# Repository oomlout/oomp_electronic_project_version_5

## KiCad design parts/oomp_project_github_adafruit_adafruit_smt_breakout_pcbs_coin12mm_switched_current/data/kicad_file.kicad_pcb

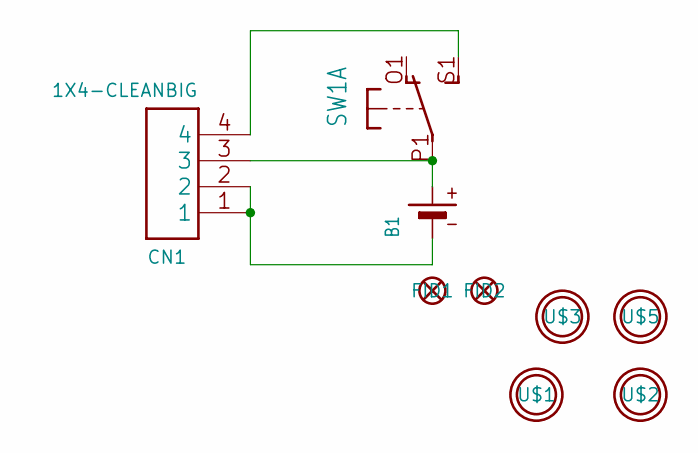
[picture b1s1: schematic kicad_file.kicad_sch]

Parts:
B1: BATTERYCR1220_SMT; CR1220
CN1: 1X4-CLEANBIG; 1X04-CLEANBIG
FID1, FID2: FIDUCIAL""; FIDUCIAL_1MM
SW1: DPDT-EG1390; EG1390
U$1, U$2, U$3, U$5: MOUNTINGHOLE2.5; MOUNTINGHOLE_2.5_PLATED

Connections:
3V: B1.+$1 (+), CN1.3, SW1.P1
unnamed: B1.-, CN1.1, CN1.2
unnamed: CN1.4, SW1.S1 (S)

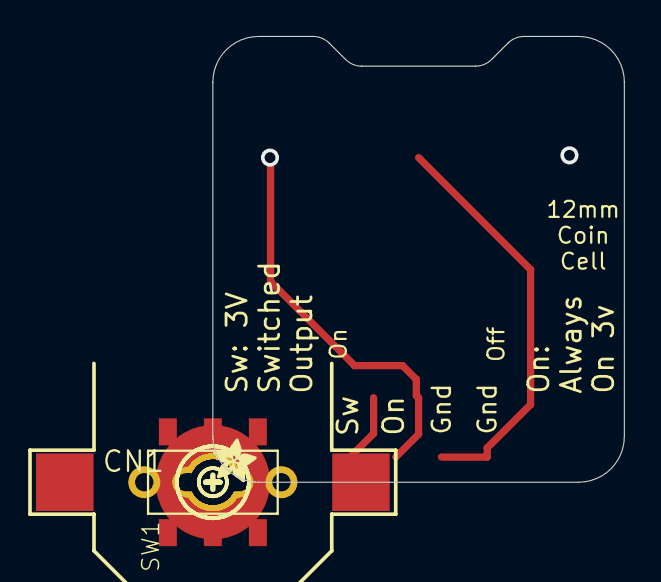
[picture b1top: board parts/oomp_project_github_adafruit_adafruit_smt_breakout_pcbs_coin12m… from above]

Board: 2 copper layers, 22.9 x 24.8 mm, 12 parts (0 on the bottom side), 3 nets.

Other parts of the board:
U$6: SYMBOL_PLUS
U$7: SYMBOL_MINUS
U$8: ADAFRUIT_2.5MM

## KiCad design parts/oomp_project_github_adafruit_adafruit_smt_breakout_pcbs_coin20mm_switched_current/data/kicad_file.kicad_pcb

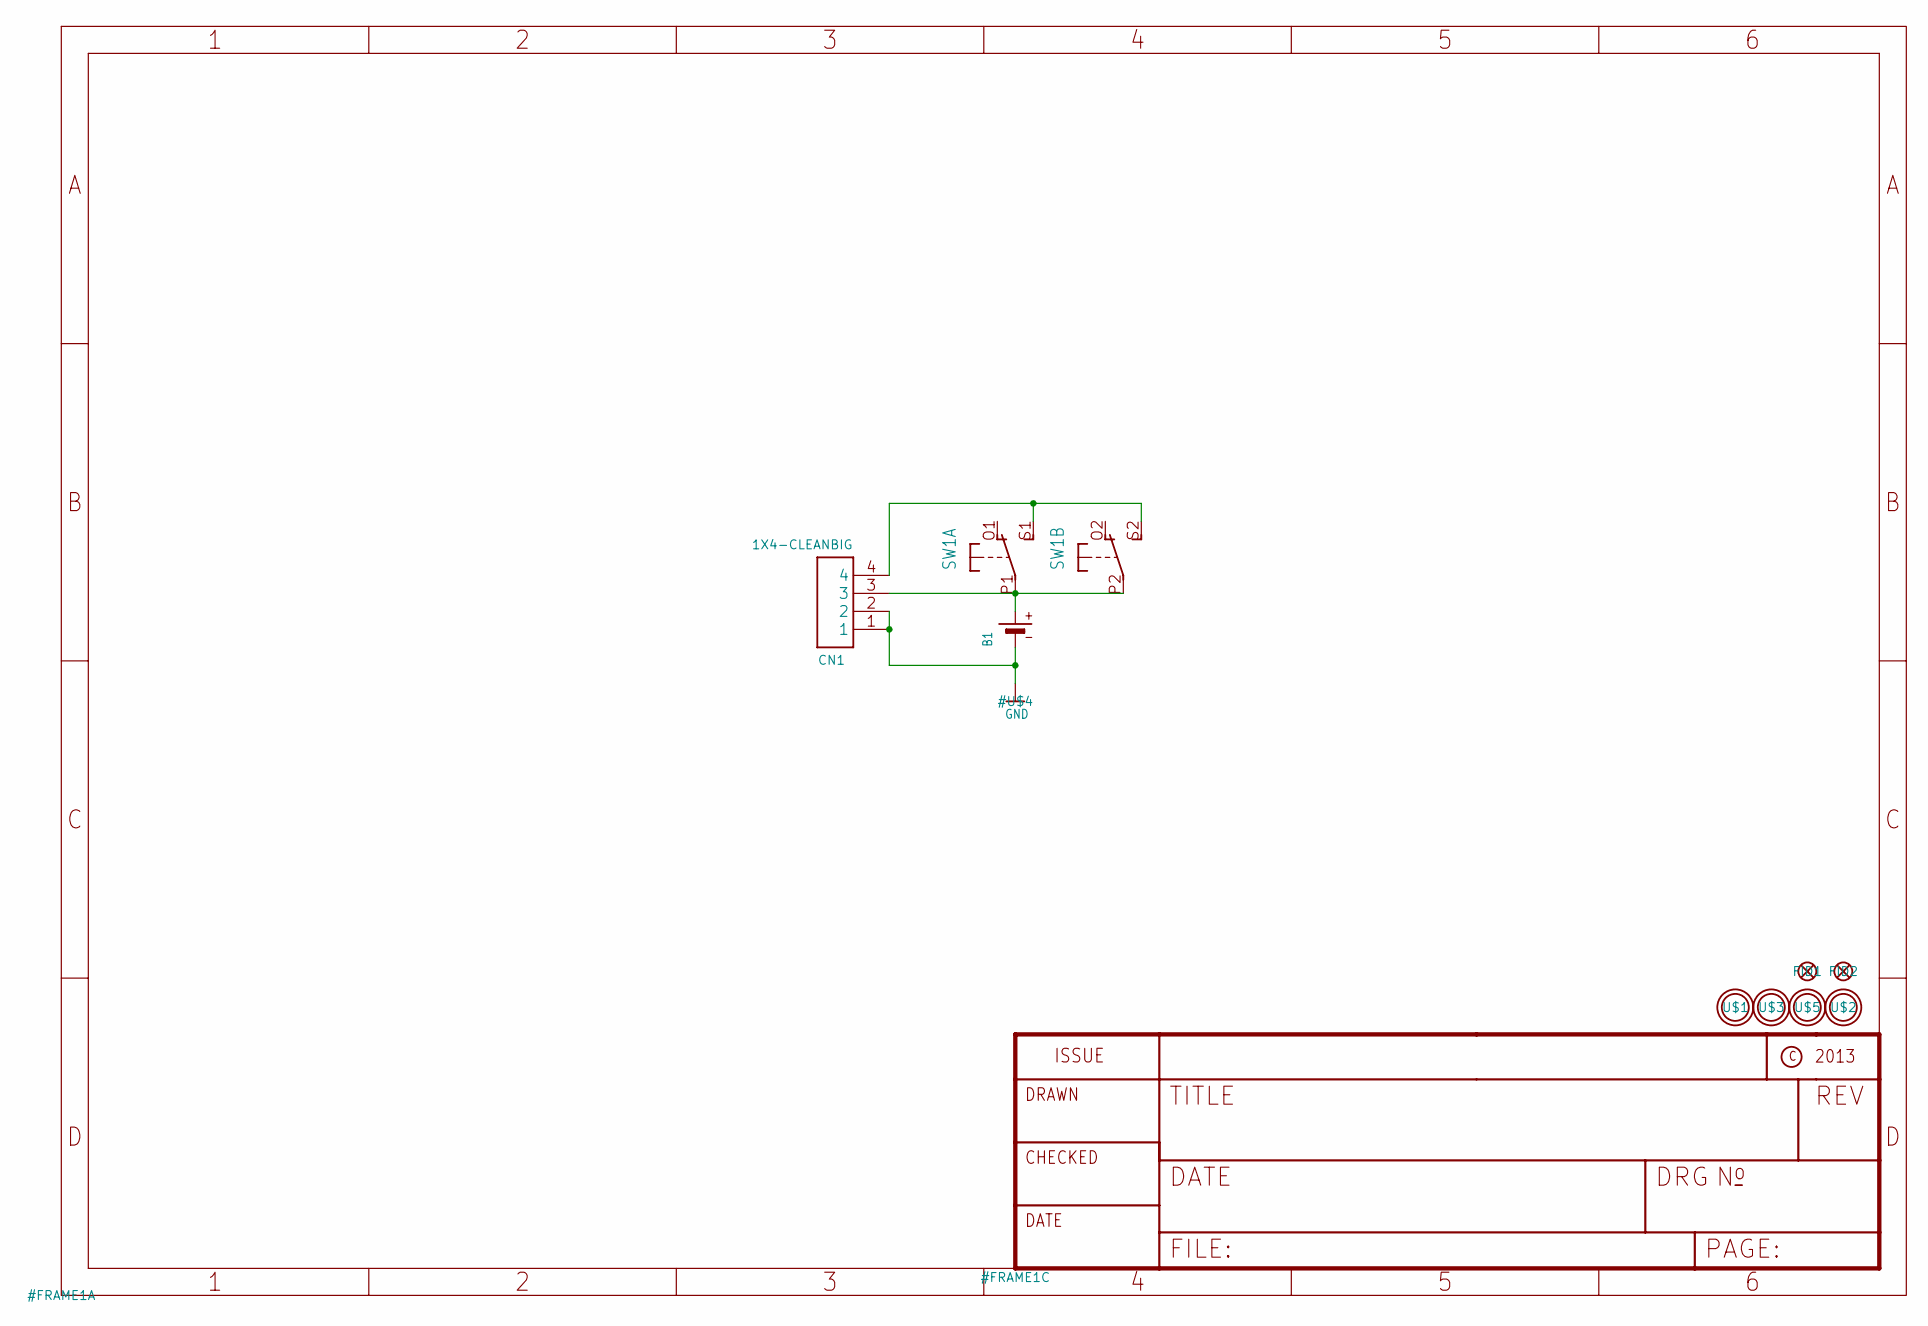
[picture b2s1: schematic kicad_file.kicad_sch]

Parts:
B1: BATTERYCR2032_BAT-HLD-001; CR2032_SMT_BAT-HLD-001
CN1: 1X4-CLEANBIG; 1X04-CLEANBIG
FID1, FID2: FIDUCIAL""; FIDUCIAL_1MM
SW1: DPDT-EG1390; EG1390
U$1, U$2, U$3, U$5: MOUNTINGHOLE2.5; MOUNTINGHOLE_2.5_PLATED

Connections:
3V: B1.+$1 (+), B1.+$2 (+), CN1.3, SW1.P1, SW1.P2
GND: B1.-, CN1.1, CN1.2
unnamed: CN1.4, SW1.S1 (S), SW1.S2 (S)

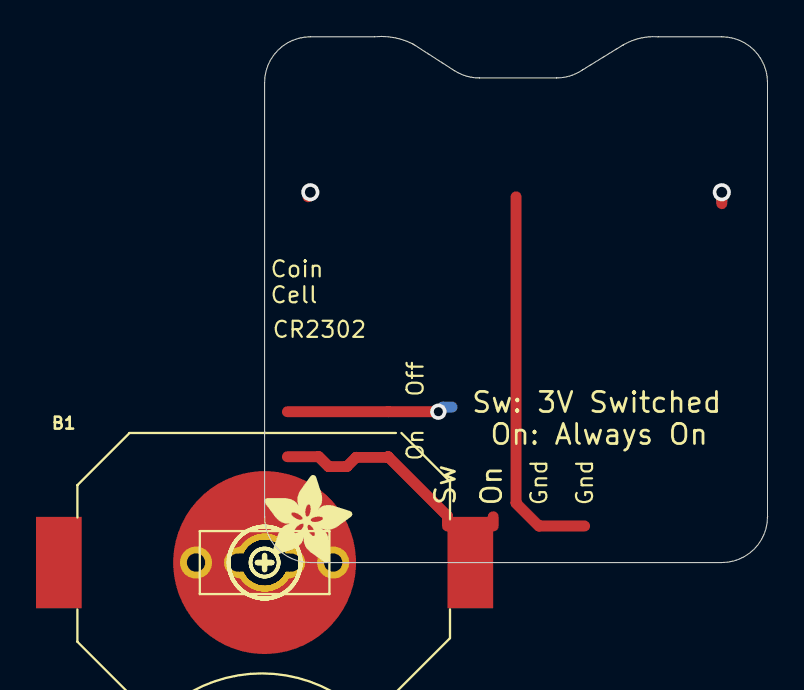
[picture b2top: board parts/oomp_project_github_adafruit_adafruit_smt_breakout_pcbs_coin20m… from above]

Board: 2 copper layers, 27.9 x 29.2 mm, 12 parts (0 on the bottom side), 3 nets.

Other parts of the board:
U$6: SYMBOL_PLUS
U$7: SYMBOL_MINUS
U$8: ADAFRUIT_5MM

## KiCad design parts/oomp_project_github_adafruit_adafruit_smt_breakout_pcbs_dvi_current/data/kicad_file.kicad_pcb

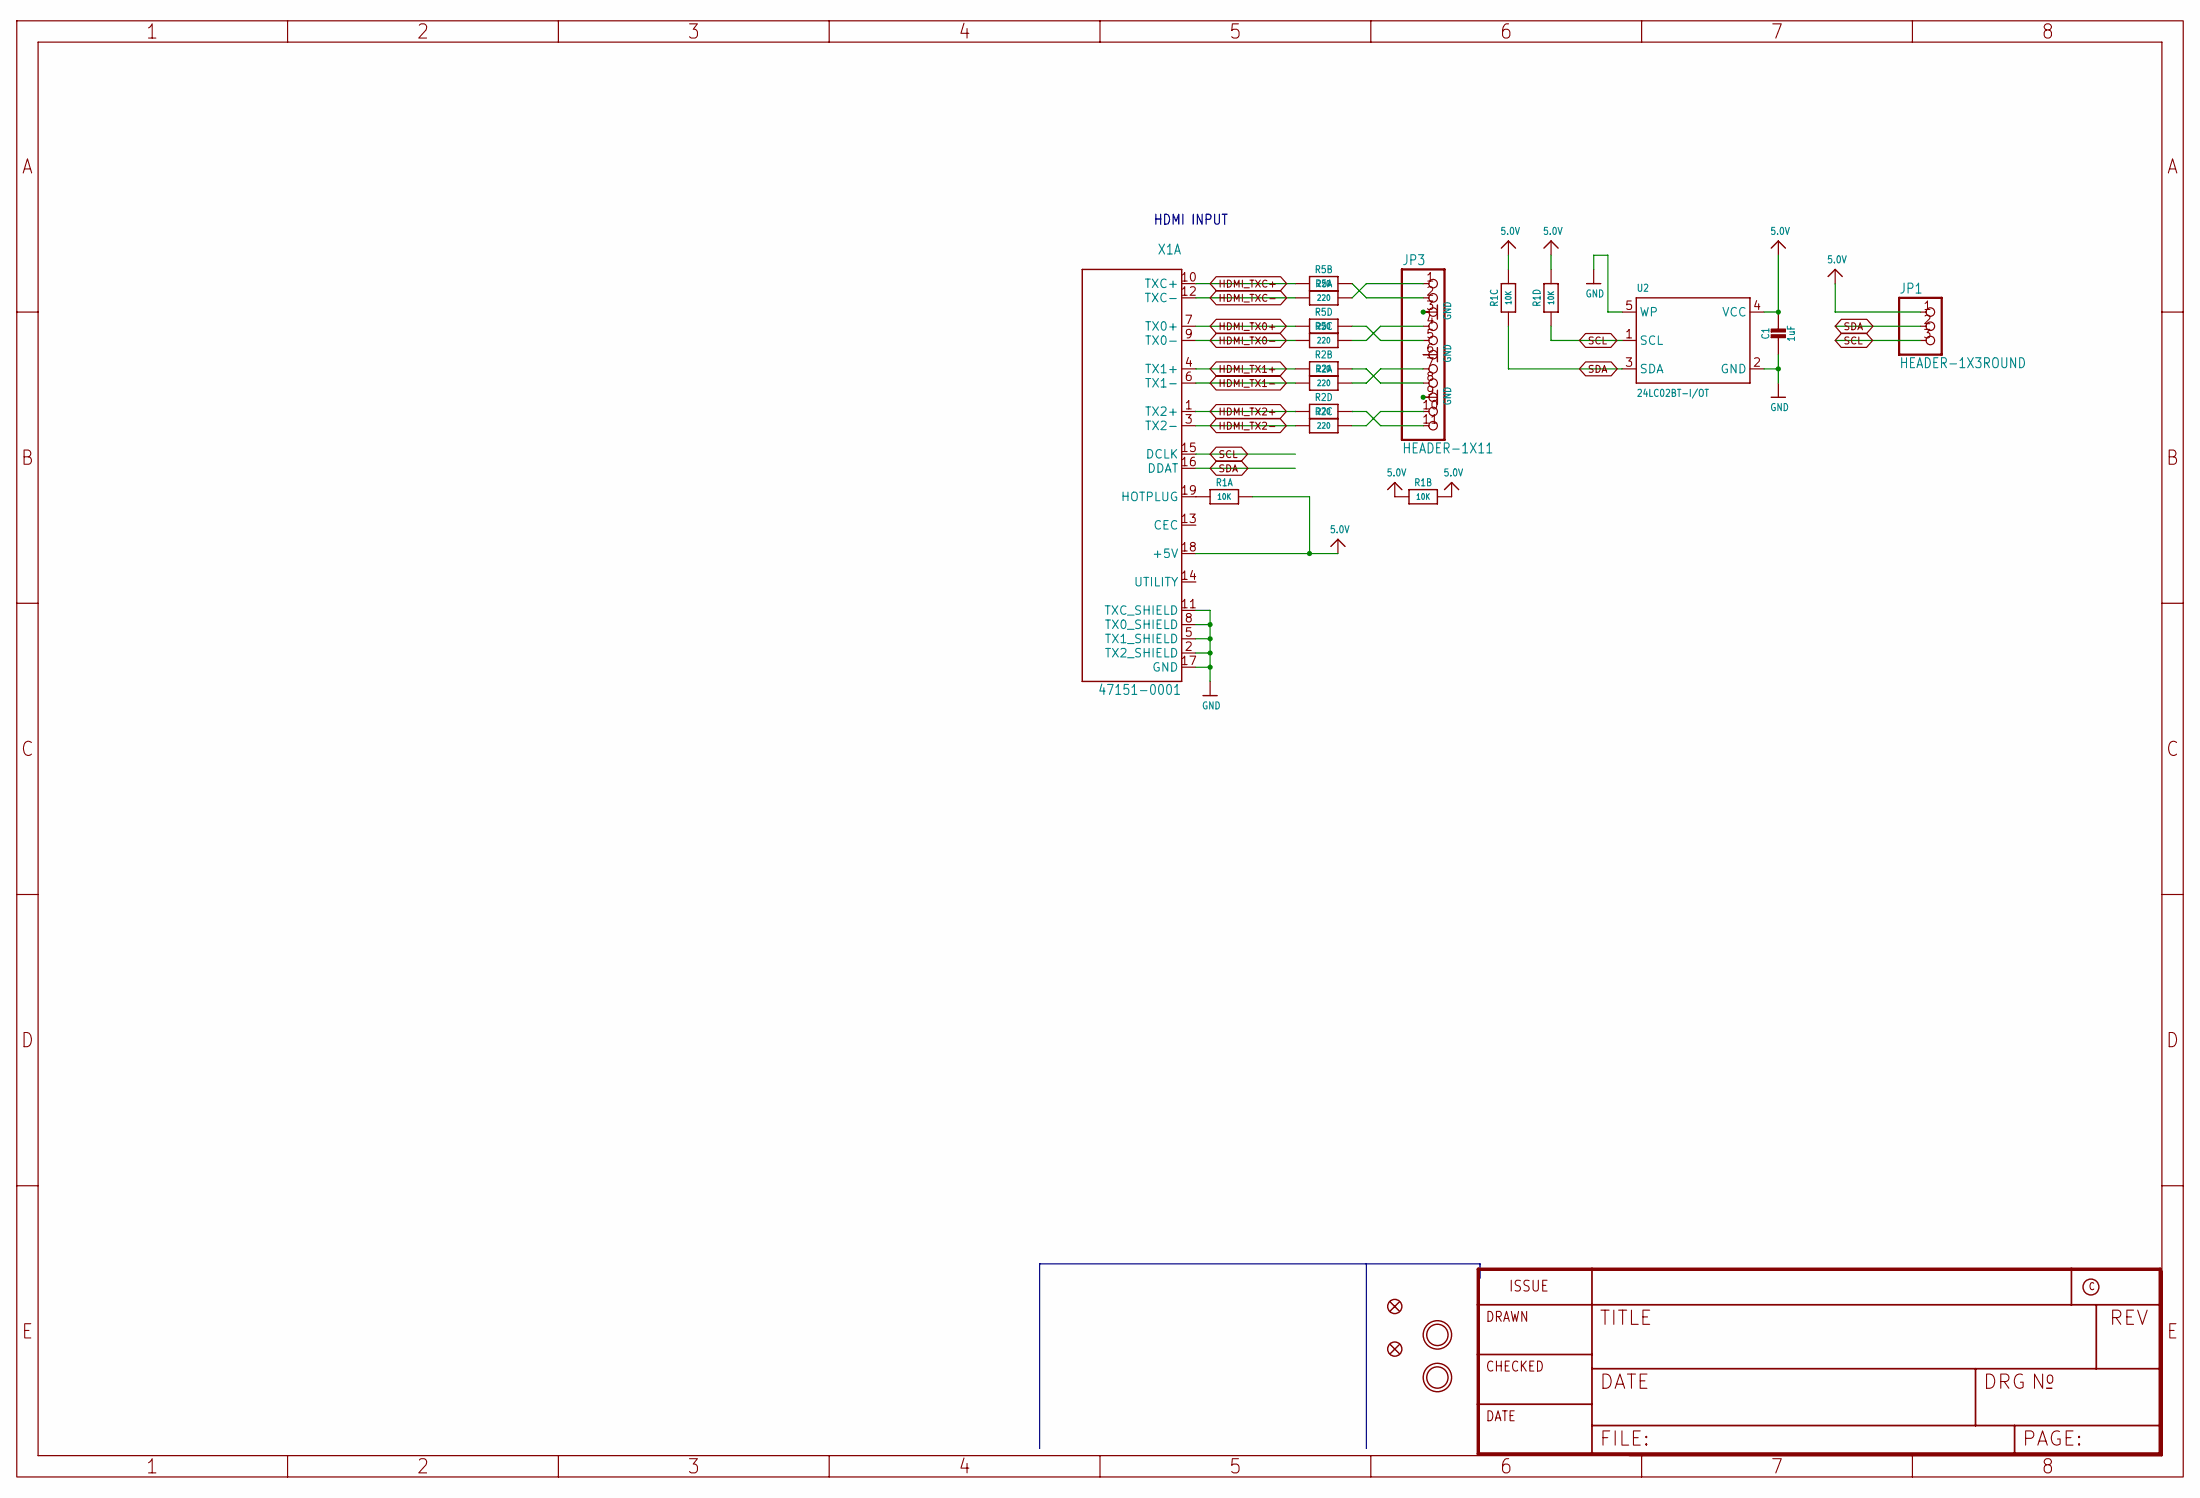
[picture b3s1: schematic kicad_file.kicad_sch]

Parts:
C1: 1uF; 0603-NO
FID1, FID2: FIDUCIAL_1MM
JP1: HEADER-1X3ROUND; 1X03_ROUND
JP3: HEADER-1X11; 1X11_ROUND
R1: 10K; RESPACK_4X0603
R2, R5: 220; RESPACK_4X0603
U2: 24LC02BT-I/OT; SOT23-5
U$32, U$33: MOUNTINGHOLE2.5; MOUNTINGHOLE_2.5_PLATED
X1: 47151-0001; HDMI_MOLEX_47151-0001

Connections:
5.0V: C1.1, JP1.1, R1.2 (1), R1.5 (2), R1.6 (2), R1.7 (2), R1.8 (2), U2.4 (VCC), X1.18 (+5V)
GND: C1.2, JP3.3, JP3.6, JP3.9, U2.2 (GND), U2.5 (WP), X1.2 (TX2_SHIELD), X1.5 (TX1_SHIELD), X1.8 (TX0_SHIELD), X1.11 (TXC_SHIELD), X1.17 (GND), X1.P$1 (GND), X1.P$2 (GND), X1.P$3 (GND), X1.P$4 (GND)
HDMI_TX0+: R5.4 (1), X1.7 (TX0+)
HDMI_TX0-: R5.3 (1), X1.9 (TX0-)
HDMI_TX1+: R2.2 (1), X1.4 (TX1+)
HDMI_TX1-: R2.1, X1.6 (TX1-)
HDMI_TX2+: R2.4 (1), X1.1 (TX2+)
HDMI_TX2-: R2.3 (1), X1.3 (TX2-)
HDMI_TXC+: R5.2 (1), X1.10 (TXC+)
HDMI_TXC-: R5.1, X1.12 (TXC-)
unnamed: R1.1, X1.19 (HOTPLUG)
SCL: JP1.3, R1.4 (1), U2.1 (SCL), X1.15 (DCLK)
SDA: JP1.2, R1.3 (1), U2.3 (SDA), X1.16 (DDAT)
TX0+: JP3.5, R5.5 (2)
TX0-: JP3.4, R5.6 (2)
TX1+: JP3.8, R2.7 (2)
TX1-: JP3.7, R2.8 (2)
TX2+: JP3.11, R2.5 (2)
TX2-: JP3.10, R2.6 (2)
TXC+: JP3.2, R5.7 (2)
TXC-: JP3.1, R5.8 (2)

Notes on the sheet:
HDMI INPUT

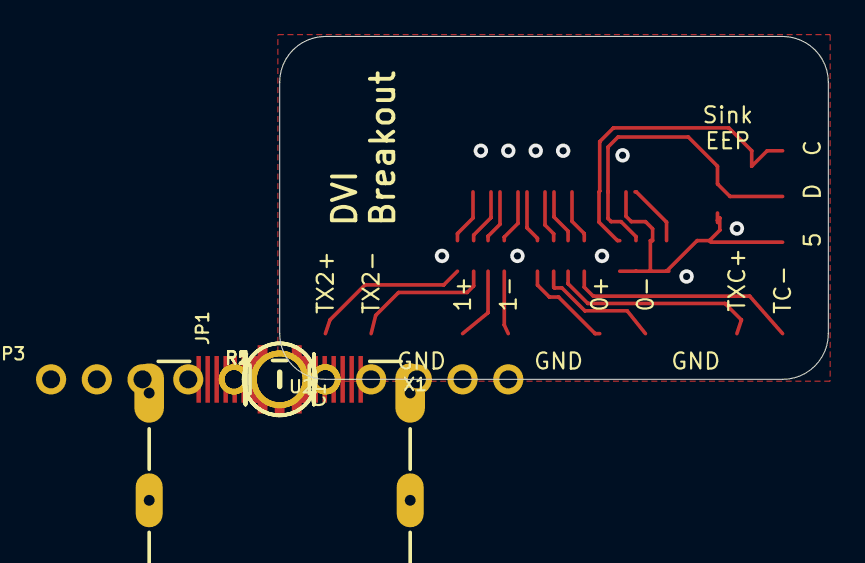
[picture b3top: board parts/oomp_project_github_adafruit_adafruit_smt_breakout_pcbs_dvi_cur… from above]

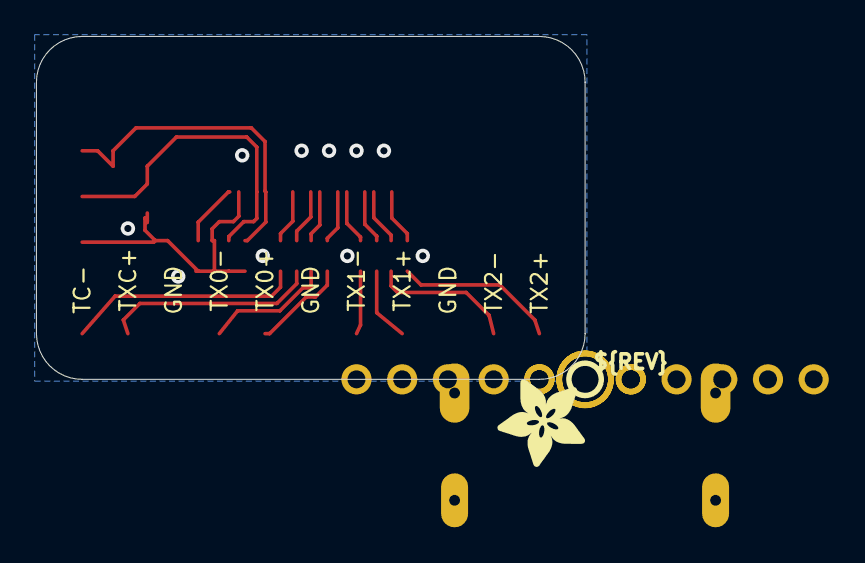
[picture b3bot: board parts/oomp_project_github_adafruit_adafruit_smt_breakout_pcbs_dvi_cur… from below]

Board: 2 copper layers, 30.5 x 19.1 mm, 14 parts (2 on the bottom side), 21 nets.

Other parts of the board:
U$6: ADAFRUIT_5MM
U$73: PCBFEAT-REV-040

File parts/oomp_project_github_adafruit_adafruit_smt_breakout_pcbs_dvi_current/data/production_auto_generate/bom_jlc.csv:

Comment,Designator,Footprint,LCSC Part #
,JP1,DVI-import-fps:1X03_ROUND,C49257
,JP3,DVI-import-fps:1X11_ROUND,C2894934
,U$6,DVI-import-fps:ADAFRUIT_5MM,
,U$73,DVI-import-fps:PCBFEAT-REV-040,
10K,R1,DVI-import-fps:RESPACK_4X0603,C98220
1uF,C1,DVI-import-fps:0603-NO,C5673
220,"R2,R5",DVI-import-fps:RESPACK_4X0603,C2907127
24LC02BT-I/OT,U2,DVI-import-fps:SOT23-5,
47151-0001,X1,DVI-import-fps:HDMI_MOLEX_47151-0001,
